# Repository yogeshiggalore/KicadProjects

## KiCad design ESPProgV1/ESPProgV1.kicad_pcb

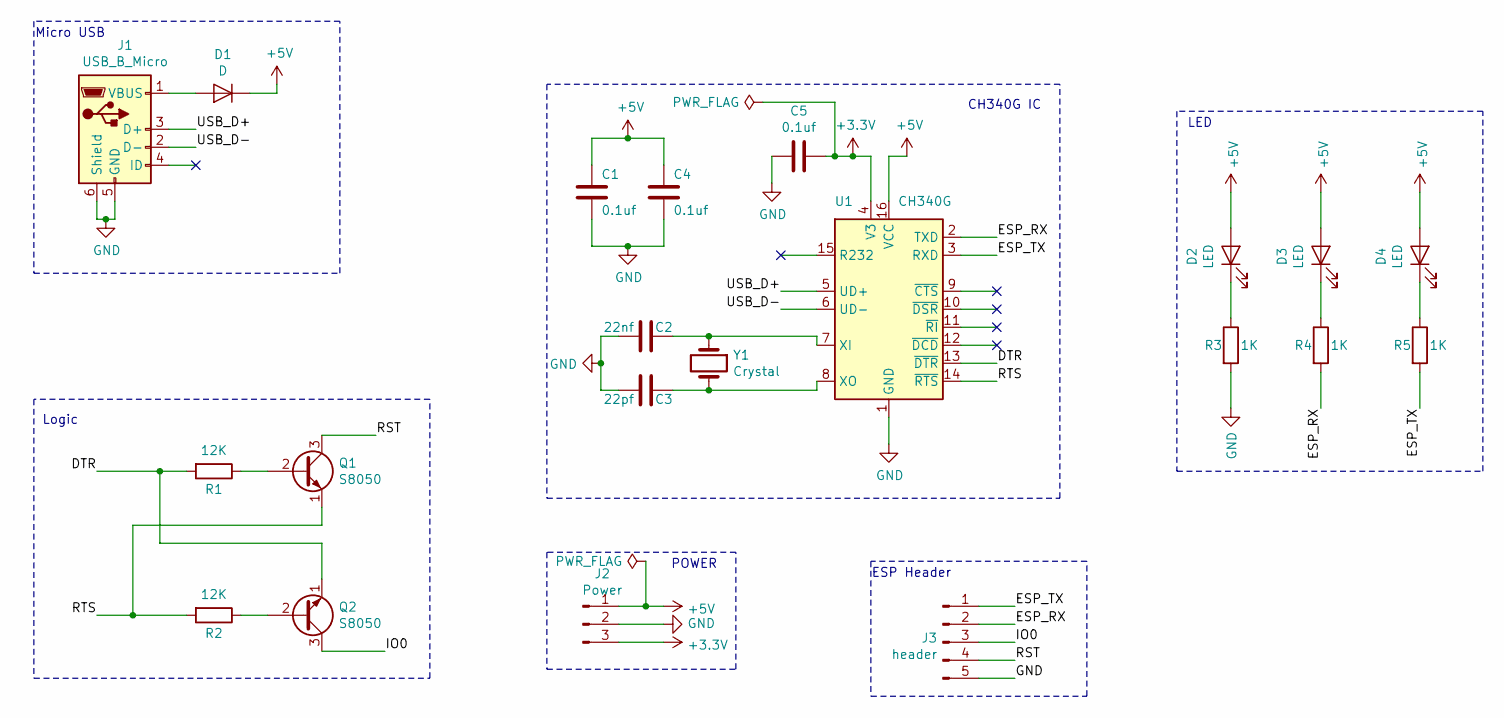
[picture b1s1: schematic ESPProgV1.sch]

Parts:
C1, C4, C5: 0.1uf; C_0805_2012Metric_Pad1.15x1.40mm_HandSolder
C2: 22nf; C_0805_2012Metric_Pad1.15x1.40mm_HandSolder
C3: 22pf; C_0805_2012Metric_Pad1.15x1.40mm_HandSolder
D1: D; D_SMB
D2, D3, D4: LED; LED_0805_2012Metric_Pad1.15x1.40mm_HandSolder
J1: USB_B_Micro; USB_Micro-B_Wuerth_629105150521
J2: Power; PinHeader_1x03_P2.54mm_Vertical
J3: header; PinHeader_1x05_P2.54mm_Vertical
Q1, Q2: S8050; SOT-23
R1, R2: 12K; R_0805_2012Metric_Pad1.15x1.40mm_HandSolder
R3, R4, R5: 1K; R_0805_2012Metric_Pad1.15x1.40mm_HandSolder
U1: CH340G; SOIC-16_3.9x9.9mm_P1.27mm
Y1: Crystal; XTAL_ECS-120-20-46X

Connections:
+3V3: C5.1, J2.3, U1.4 (V3)
+5V: C1.1, C4.1, D1.1 (K), D2.2 (A), D3.2 (A), D4.2 (A), J2.1, U1.16 (VCC)
/DTR: Q2.1 (E), R1.2, U1.13 (~DTR)
/ESP_RX: J3.2, R4.2, U1.2 (TXD)
/ESP_TX: J3.1, R5.2, U1.3 (RXD)
/IO0: J3.3, Q2.3 (C)
/RST: J3.4, Q1.3 (C)
/RTS: Q1.1 (E), R2.2, U1.14 (~RTS)
/USB_D+: J1.3 (D+), U1.5 (UD+)
/USB_D-: J1.2 (D-), U1.6 (UD-)
GND: C1.2, C2.2, C3.2, C4.2, C5.2, J1.5 (GND), J1.6 (Shield), J2.2, J3.5, R3.2, U1.1 (GND)
unnamed: C2.1, U1.7 (XI), Y1.1
unnamed: C3.1, U1.8 (XO), Y1.2
unnamed: D1.2 (A), J1.1 (VBUS)
unnamed: D2.1 (K), R3.1
unnamed: D3.1 (K), R4.1
unnamed: D4.1 (K), R5.1
unnamed: Q1.2 (B), R1.1
unnamed: Q2.2 (B), R2.1

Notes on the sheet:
Micro USB
LED
ESP Header
Logic
CH340G IC
POWER

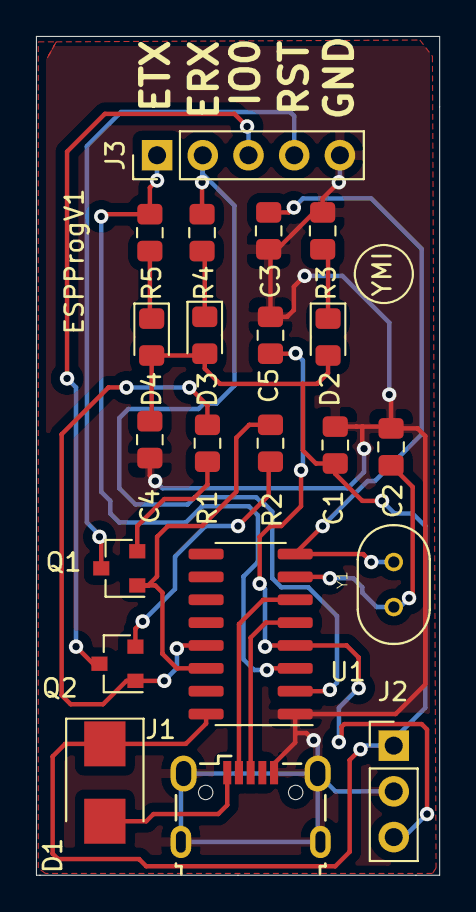
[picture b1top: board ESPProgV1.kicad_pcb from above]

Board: 2 copper layers, 22.4 x 46.6 mm, 21 parts (0 on the bottom side), 19 nets.

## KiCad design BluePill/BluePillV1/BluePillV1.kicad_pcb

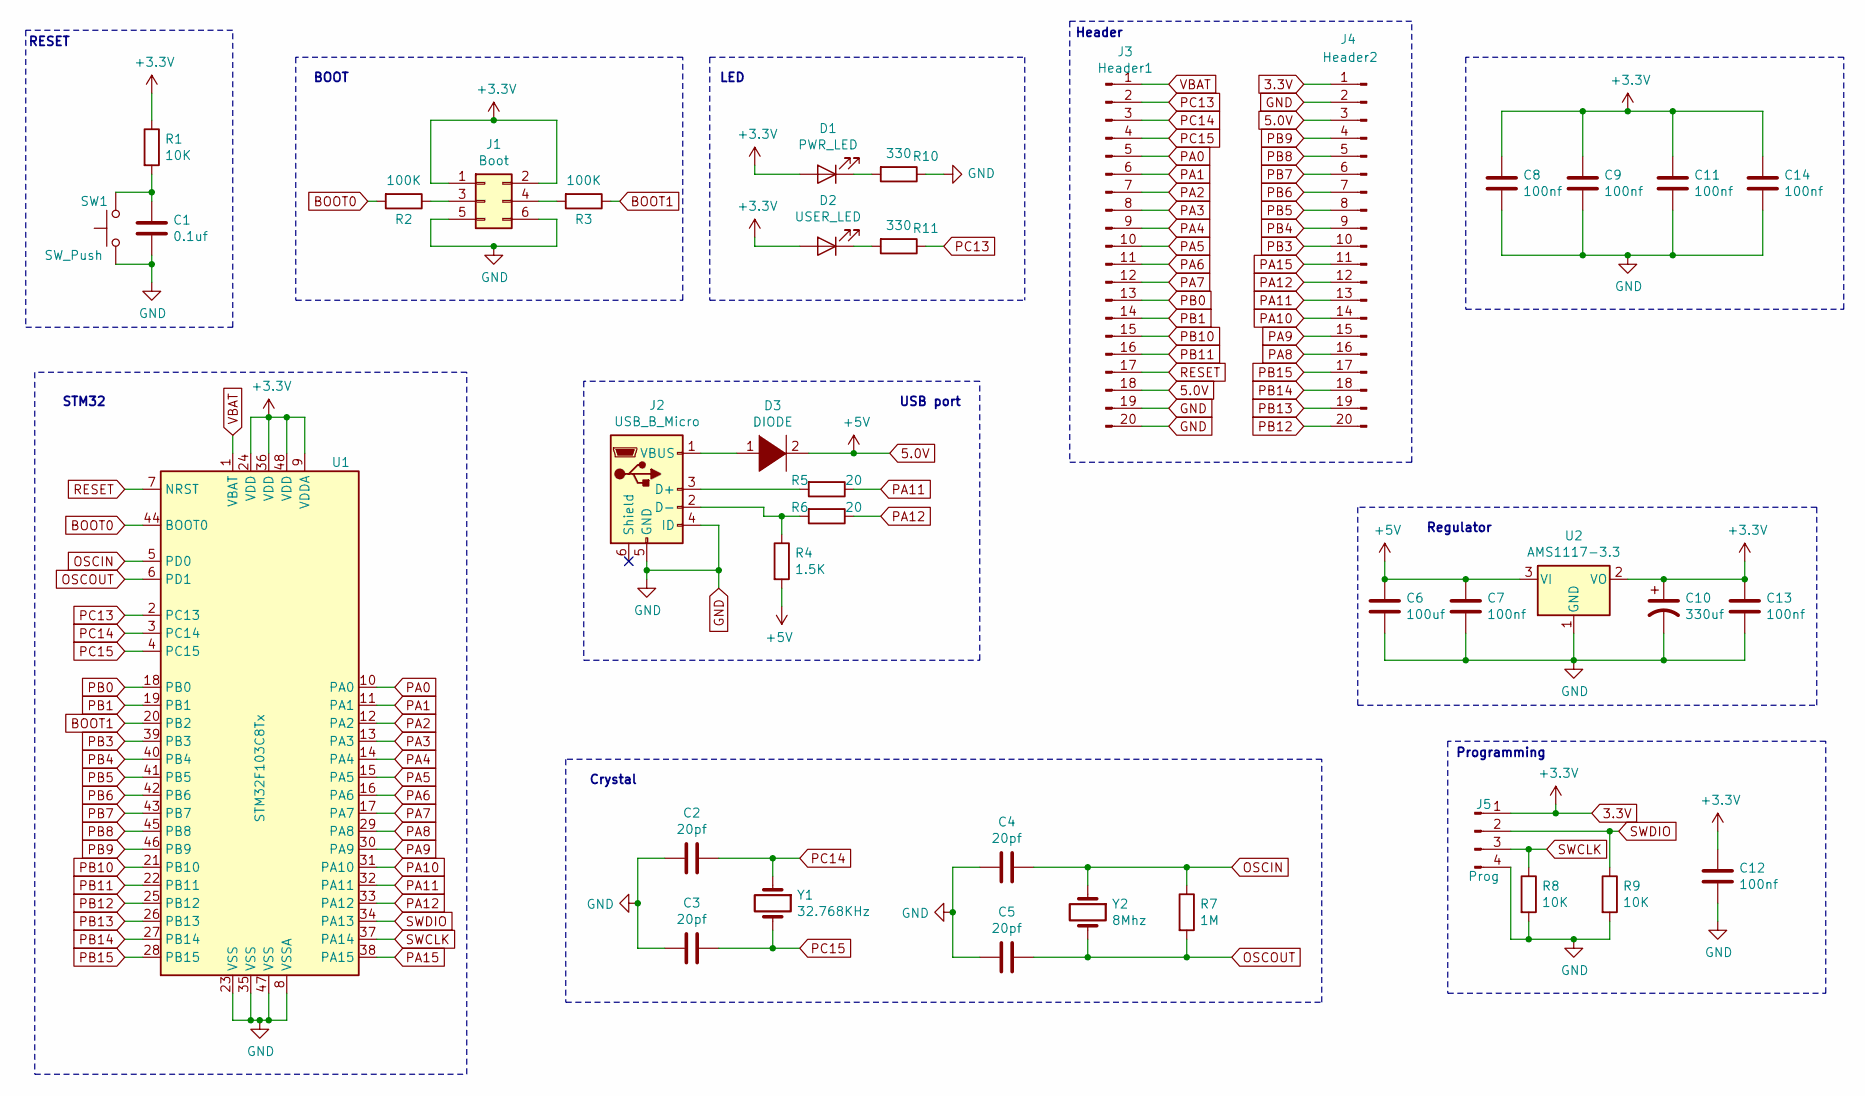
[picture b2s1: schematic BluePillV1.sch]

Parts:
C1: 0.1uf; C_0805_2012Metric_Pad1.15x1.40mm_HandSolder
C2, C3, C4, C5: 20pf; C_0805_2012Metric_Pad1.15x1.40mm_HandSolder
C6: 100uf; C_0805_2012Metric_Pad1.15x1.40mm_HandSolder
C7, C8, C9, C11, C12, C13, C14: 100nf; C_0805_2012Metric_Pad1.15x1.40mm_HandSolder
C10: 330uf; CP_Elec_4x5.4
D1: PWR_LED; LED_0805_2012Metric_Pad1.15x1.40mm_HandSolder
D2: USER_LED; LED_0805_2012Metric_Pad1.15x1.40mm_HandSolder
D3: DIODE; LED_0805_2012Metric_Pad1.15x1.40mm_HandSolder
J1: Boot; PinHeader_2x03_P2.54mm_Vertical
J2: USB_B_Micro; USB_Micro-B_Wuerth_629105150521
J3: Header1; PinHeader_1x20_P2.54mm_Vertical
J4: Header2; PinHeader_1x20_P2.54mm_Vertical
J5: Prog; PinHeader_1x04_P2.54mm_Vertical
R1, R8, R9: 10K; R_0805_2012Metric_Pad1.15x1.40mm_HandSolder
R2, R3: 100K; R_0805_2012Metric_Pad1.15x1.40mm_HandSolder
R4: 1.5K; R_0805_2012Metric_Pad1.15x1.40mm_HandSolder
R5, R6: 20; R_0805_2012Metric_Pad1.15x1.40mm_HandSolder
R7: 1M; R_0805_2012Metric_Pad1.15x1.40mm_HandSolder
R10, R11: 330; R_0805_2012Metric_Pad1.15x1.40mm_HandSolder
SW1: SW_Push; TE_3-1825910-1
U1: STM32F103C8Tx; LQFP-48_7x7mm_P0.5mm
U2: AMS1117-3.3; SOT-223-3_TabPin2
Y1: 32.768KHz; Crystal_AT310_D3.0mm_L10.0mm_Horizontal
Y2: 8Mhz; XTAL_ECS-120-20-46X

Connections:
3.3V: C8.1, C9.1, C10.1, C11.1, C12.1, C13.1, C14.1, D1.2 (A), D2.2 (A), J1.1, J1.2, J4.1, J5.1, R1.1, U1.9 (VDDA), U1.24 (VDD), U1.36 (VDD), U1.48 (VDD), U2.2 (VO)
5.0V: C6.1, C7.1, D3.2 (A), J3.18, J4.3, R4.2, U2.3 (VI)
BOOT0: R2.2, U1.44 (BOOT0)
BOOT1: R3.1, U1.20 (PB2)
GND: C1.2, C2.2, C3.2, C4.2, C5.2, C6.2, C7.2, C8.2, C9.2, C10.2, C11.2, C12.2, C13.2, C14.2, J1.5, J1.6, J2.4 (ID), J2.5 (GND), J3.19, J3.20, J4.2, J5.4, R8.2, R9.2, R10.1, SW1.1, U1.8 (VSSA), U1.23 (VSS), U1.35 (VSS), U1.47 (VSS), U2.1 (GND)
unnamed: C1.1, R1.2, SW1.2
unnamed: D1.1 (K), R10.2
unnamed: D2.1 (K), R11.2
unnamed: D3.1 (K), J2.1 (VBUS)
unnamed: J1.3, R2.1
unnamed: J1.4, R3.2
unnamed: J2.2 (D-), R4.1, R6.2
unnamed: J2.3 (D+), R5.2
OSCIN: C4.1, R7.1, U1.5 (PD0), Y2.1
OSCOUT: C5.1, R7.2, U1.6 (PD1), Y2.2
PA0: J3.5, U1.10 (PA0)
PA1: J3.6, U1.11 (PA1)
PA2: J3.7, U1.12 (PA2)
PA3: J3.8, U1.13 (PA3)
PA4: J3.9, U1.14 (PA4)
PA5: J3.10, U1.15 (PA5)
PA6: J3.11, U1.16 (PA6)
PA7: J3.12, U1.17 (PA7)
PA8: J4.16, U1.29 (PA8)
PA9: J4.15, U1.30 (PA9)
PA10: J4.14, U1.31 (PA10)
PA11: J4.13, R5.1, U1.32 (PA11)
PA12: J4.12, R6.1, U1.33 (PA12)
PA15: J4.11, U1.38 (PA15)
PB0: J3.13, U1.18 (PB0)
PB1: J3.14, U1.19 (PB1)
PB3: J4.10, U1.39 (PB3)
PB4: J4.9, U1.40 (PB4)
PB5: J4.8, U1.41 (PB5)
PB6: J4.7, U1.42 (PB6)
PB7: J4.6, U1.43 (PB7)
PB8: J4.5, U1.45 (PB8)
PB9: J4.4, U1.46 (PB9)
PB10: J3.15, U1.21 (PB10)
PB11: J3.16, U1.22 (PB11)
PB12: J4.20, U1.25 (PB12)
PB13: J4.19, U1.26 (PB13)
PB14: J4.18, U1.27 (PB14)
PB15: J4.17, U1.28 (PB15)
PC13: J3.2, R11.1, U1.2 (PC13)
PC14: C2.1, J3.3, U1.3 (PC14), Y1.1
PC15: C3.1, J3.4, U1.4 (PC15), Y1.2
RESET: J3.17, U1.7 (NRST)
SWCLK: J5.3, R8.1, U1.37 (PA14)
SWDIO: J5.2, R9.1, U1.34 (PA13)
VBAT: J3.1, U1.1 (VBAT)

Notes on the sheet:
RESET
BOOT
LED
Header
Regulator
STM32
USB port
Crystal
Programming

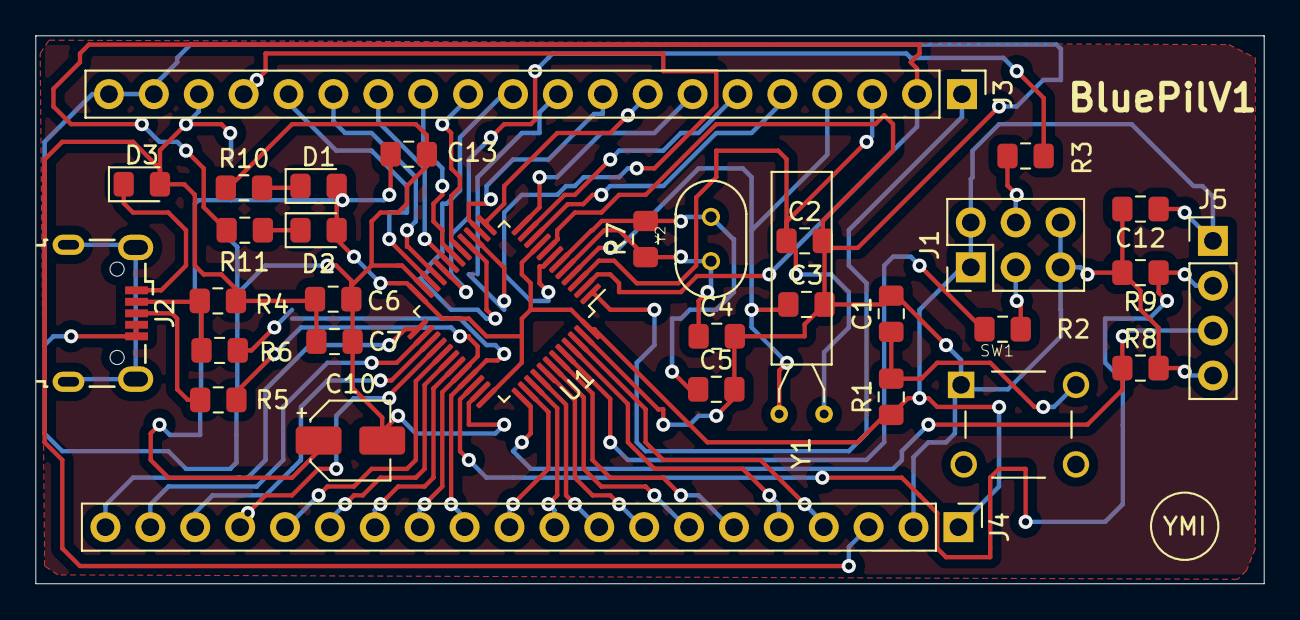
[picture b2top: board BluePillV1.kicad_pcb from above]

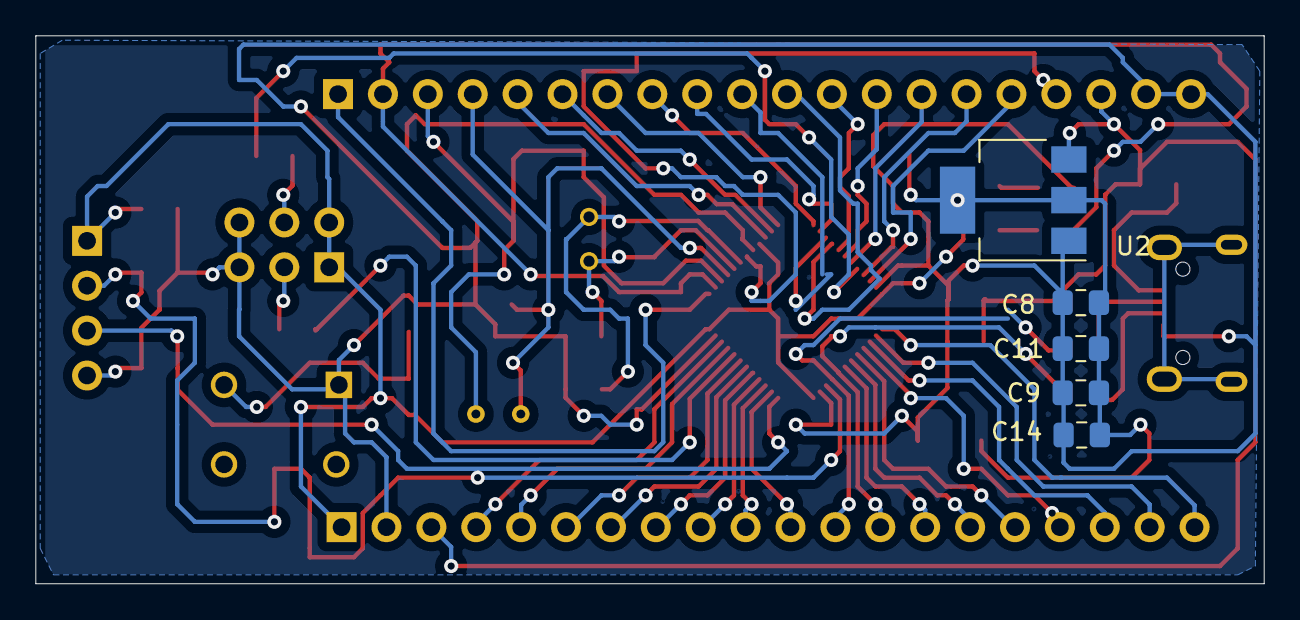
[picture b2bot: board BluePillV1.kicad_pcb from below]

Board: 2 copper layers, 69.5 x 31.0 mm, 38 parts (5 on the bottom side), 51 nets.

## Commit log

2020-09-30 ESPProgV1
    ESPProgV1 commit
2020-10-06 BluePill board
    BluePill board with STM32 microcontroller
